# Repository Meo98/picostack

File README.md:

<h1 align="center">PicoStack</h1>

<p align="center">
  <b>Stackable, contract-driven modules for the Raspberry Pi Pico. No module firmware: the Pico drives everything.</b><br>
  Open hardware, generated by code, verified by tests that are proven to fail.
</p>

<p align="center">

</p>

---

**One board plus a Pico is a working device.** Every PicoStack module is a
74 × 58 mm board with two 1×20 stacking sockets in the Pico's own geometry.
The Pico plugs into the top of the stack; all 40 pins run down through it.
Each module carries its own 6–30 V input (reverse-polarity protection,
TVS, a 3 A buck to 5 V, a Schottky into VSYS), so you can also just power
the Pico over USB while you program it and the module's logic is live.

**v3 is deliberately dumb.** v1/v2 gave every module its own microcontroller,
a token chain to address it and a bootloader path to flash it through the
stack. None of that ever ran on a desk, and none of it was needed for the
exhibits this was built for. v3 removes it: the Pico drives each channel
directly through a GPIO *bank*. The 16 PWM-capable pins GP7–GP22 are split
into four banks (A–D) of four; a module picks its bank with a 0603 solder
matrix on the board (factory default: motor = A, dimmer = B, so one motor
and one dimmer stack without touching an iron). GP26–28 serve analog
signals, GP4/GP5 come out as a Qwiic port, GP6 is a wired-AND emergency
stop, GP0–GP3 sit on a user header.

```python
import picostack                      # firmware/pico/picostack.py (MicroPython)
led = picostack.Dimmer(kanaele=4)     # bank B by default
led.set(1, 0.5)                       # channel 1 at 50 %
```

**The unusual part: these boards are not drawn, they are built.**
Schematics, placement, routing, ground stitching and the manufacturing
checks all come from Python that runs headless against KiCad. The stack's
mechanical and electrical rules live in one machine-readable file, the
*contract* ([`tools/stack_spec.py`](tools/stack_spec.py), rendered as
[docs/vertrag.md](docs/vertrag.md)), and every board is measured against it
before it may exist. The full v3 rationale is in the
[design spec](docs/superpowers/specs/2026-11-15-picostack-v3-design.md).

## Boards (v3, contract v4)

| Board | What it does | State |
|---|---|---|
| Dimmer1 / Dimmer3 / Dimmer4 | 1, 3 or 4 low-side PWM channels, 3 A each (4 A per module), screw terminals | routed, DRC 0/0, fab files in `hardware/fertigung/` |
| Motor | DRV8876 H-bridge, 2.5 A, hardware emergency stop, current sense on GP26 | next: rebuilt on the v3 contract |

Placement follows the current, not the autorouter: FETs sit right above
their terminals (tab down, leads up), free-wheel diodes above the FETs,
the buck converter under the Pico at the USB end, the 4 A trunk is
pre-wired by hand (1.4 mm) and the router only fills in the signals.
The Pico W antenna zone between the socket rows is copper-free on both
layers.

## Why you might care

- **You want motorized / sensor / whatever hats for the Pico** that stack
  instead of sprawling across a desk, with industrial-ish screw terminals
  and a 6–30 V input, and you'd rather not maintain firmware for a second
  microcontroller on every board.
- **You want to see a fully generative KiCad workflow**: schematic
  generators, a hand-placed description, headless routing
  ([KiCadRoutingTools](https://github.com/drandyhaas/KiCadRoutingTools)),
  copper-pour healing (`tools/pcb/masseheiler.py`), DRC and a
  current-capacity gate that walks every power net's real copper path
  (`tools/pcb/strombelastung.py`), all from the command line
  (`tools/pcb/verlegen_v3.sh dimmer4`).
- **You like tests that can actually fail.** Every check in this repository
  ships with a proof that it turns red when the thing it guards is broken.
  ERC and DRC caught *none* of the real bugs found during development,
  including a fail-unsafe emergency-stop gate, a reverse-polarity FET wired
  as a crowbar, a 0.25 mm neck in a 4 A trunk, and a board height at which
  a module mounted upside-down would have plugged in. See
  [tests/](tests/) and `tests/run_all.py`.

## Repository layout

```text
tools/stack_spec.py   the contract (v4)
tools/sch/            schematic generators (versorgung.py, dimmermodul.py)
tools/pcb/            placement descriptions, build.py, router driver, probes
tools/fertigung.sh    gerbers + BOM/CPL for JLCPCB
tests/                plain-python suites (no pytest needed), tests/run_all.py
firmware/pico/        MicroPython library for the Pico
hardware/kicad/       generated .kicad_sch + built .kicad_pcb per board
hardware/fertigung/   gerber zip, jlc-bom.csv, jlc-cpl.csv per board
docs/                 project website, vertrag.md, specs
```

## Building the boards yourself

You need KiCad 10, Python 3, and
[KiCadRoutingTools](https://github.com/drandyhaas/KiCadRoutingTools)
(with numpy/scipy/shapely; `verlegen_v3.sh` wraps it in a nix-shell).

```bash
python3 tests/run_all.py                 # every suite, no board tools needed
tools/pcb/verlegen_v3.sh dimmer4         # schematic -> board -> routed -> DRC + probes
tools/fertigung.sh dimmer4               # gerbers, BOM, CPL
```

## Getting boards made

Gerbers, JLC-format BOM/CPL and the list of hand-populated parts for all
three dimmer boards live under `hardware/fertigung/{dimmer1,dimmer3,dimmer4}/`.
[`hardware/fertigung/ORDERING.md`](hardware/fertigung/ORDERING.md) walks
through ordering an assembled board at JLCPCB. The stacking headers
(Pimoroni Pico Stacking Headers, 1×20 and a 1×4 cut from one) and the user
header are soldered by hand, in the plugged-together stack, so the contacts
line up without strain. **No v3 board has been manufactured yet.**

## Contributing a module

A module is a 74 × 58 mm board that keeps the contract: socket rows and
power row on their contract positions, terminals flush with the bottom
edge, nothing taller than 8 mm under the Pico, the antenna zone free, and
a bank matrix for its signals. Start by copying
`tools/pcb/spec_dimmer_basis.py` and `tools/sch/dimmermodul.py`, then read
[CONTRIBUTING.md](CONTRIBUTING.md).

## License

- **Hardware** (everything under `hardware/`): [CERN-OHL-S-2.0](hardware/LICENSE).
- **Code** (tools, generators, firmware): [GPL-3.0-or-later](LICENSE).
- **Documentation**: CC-BY-SA 4.0.

## Project language

The public face of this project is English. Code comments are German,
they carry the engineering rationale of every decision. New contributions
should be in English.

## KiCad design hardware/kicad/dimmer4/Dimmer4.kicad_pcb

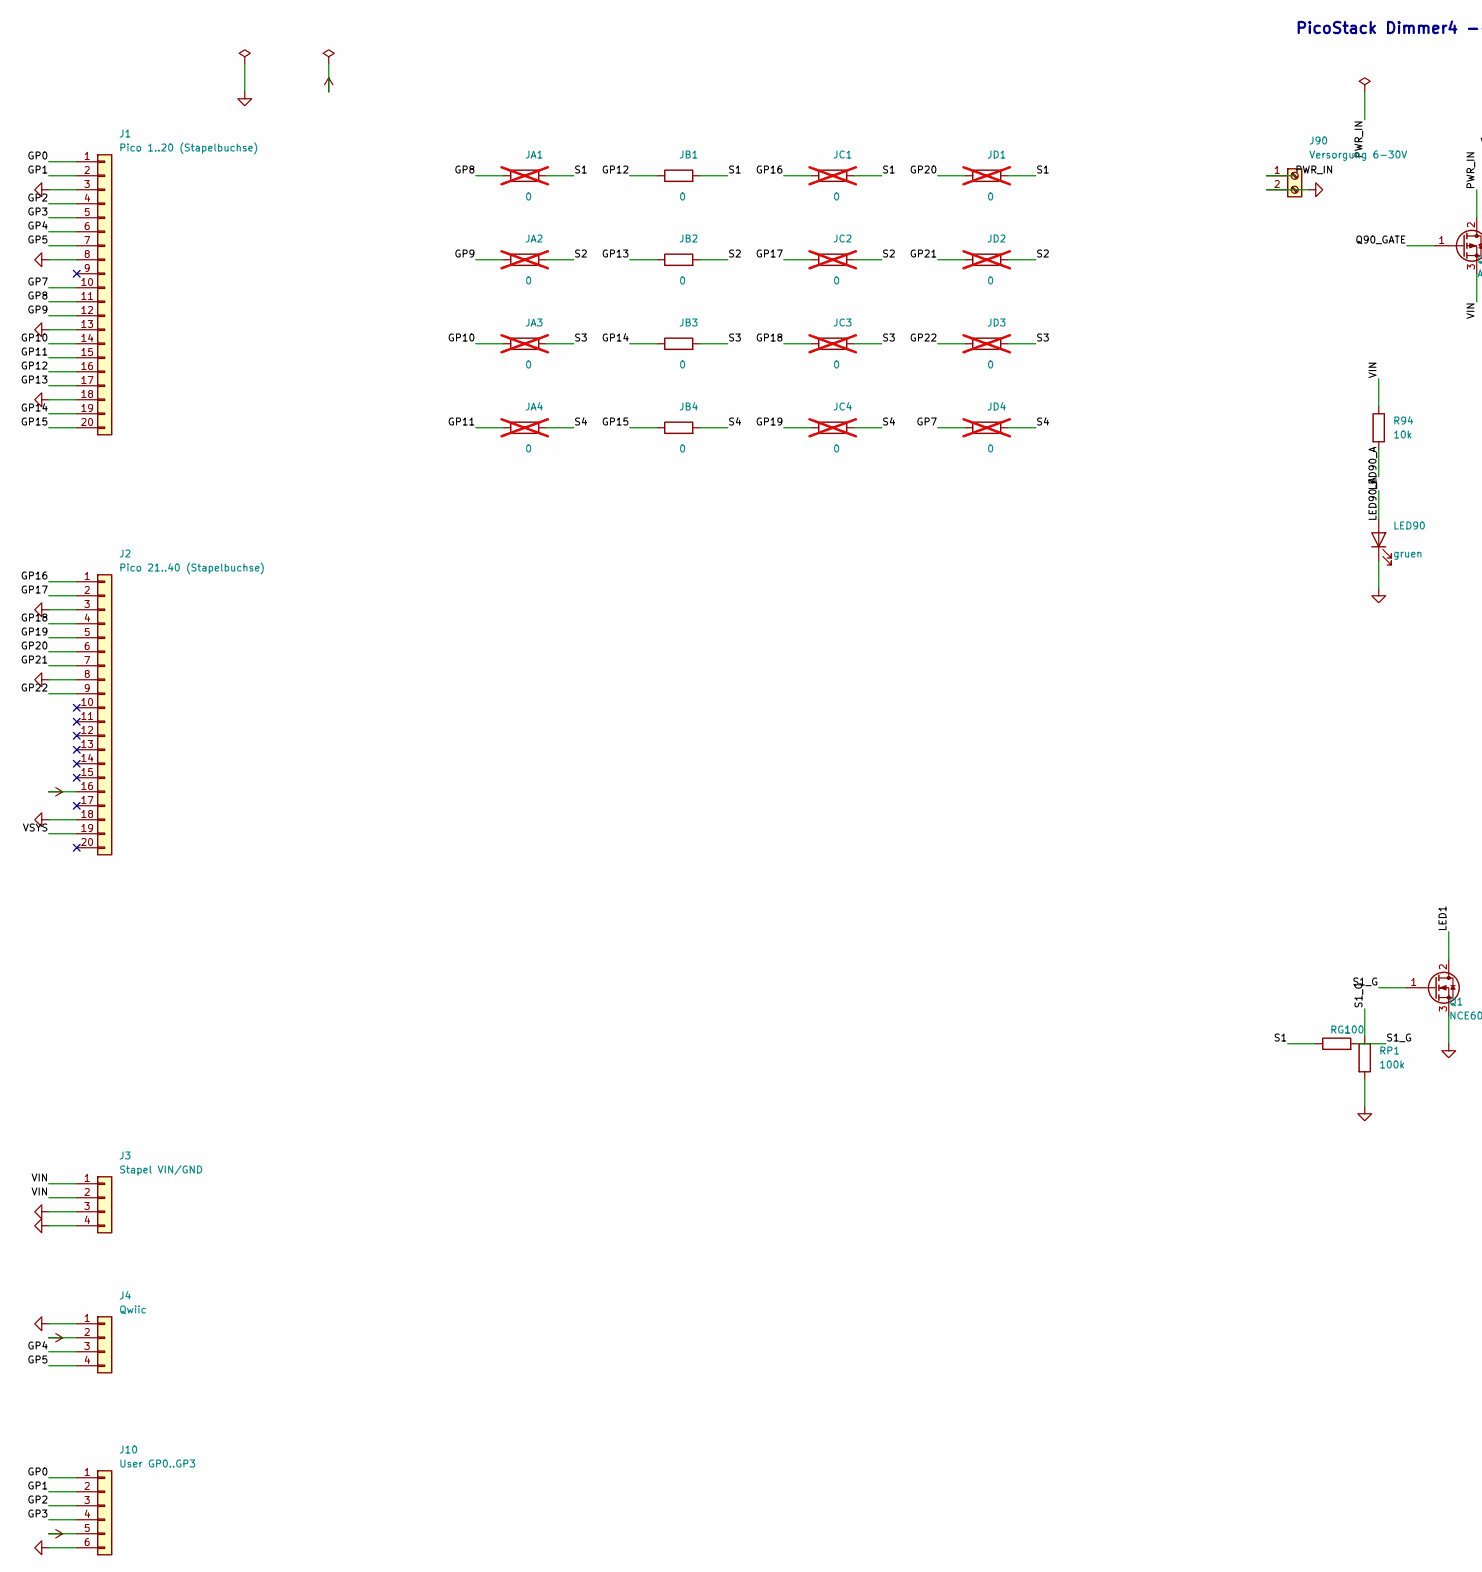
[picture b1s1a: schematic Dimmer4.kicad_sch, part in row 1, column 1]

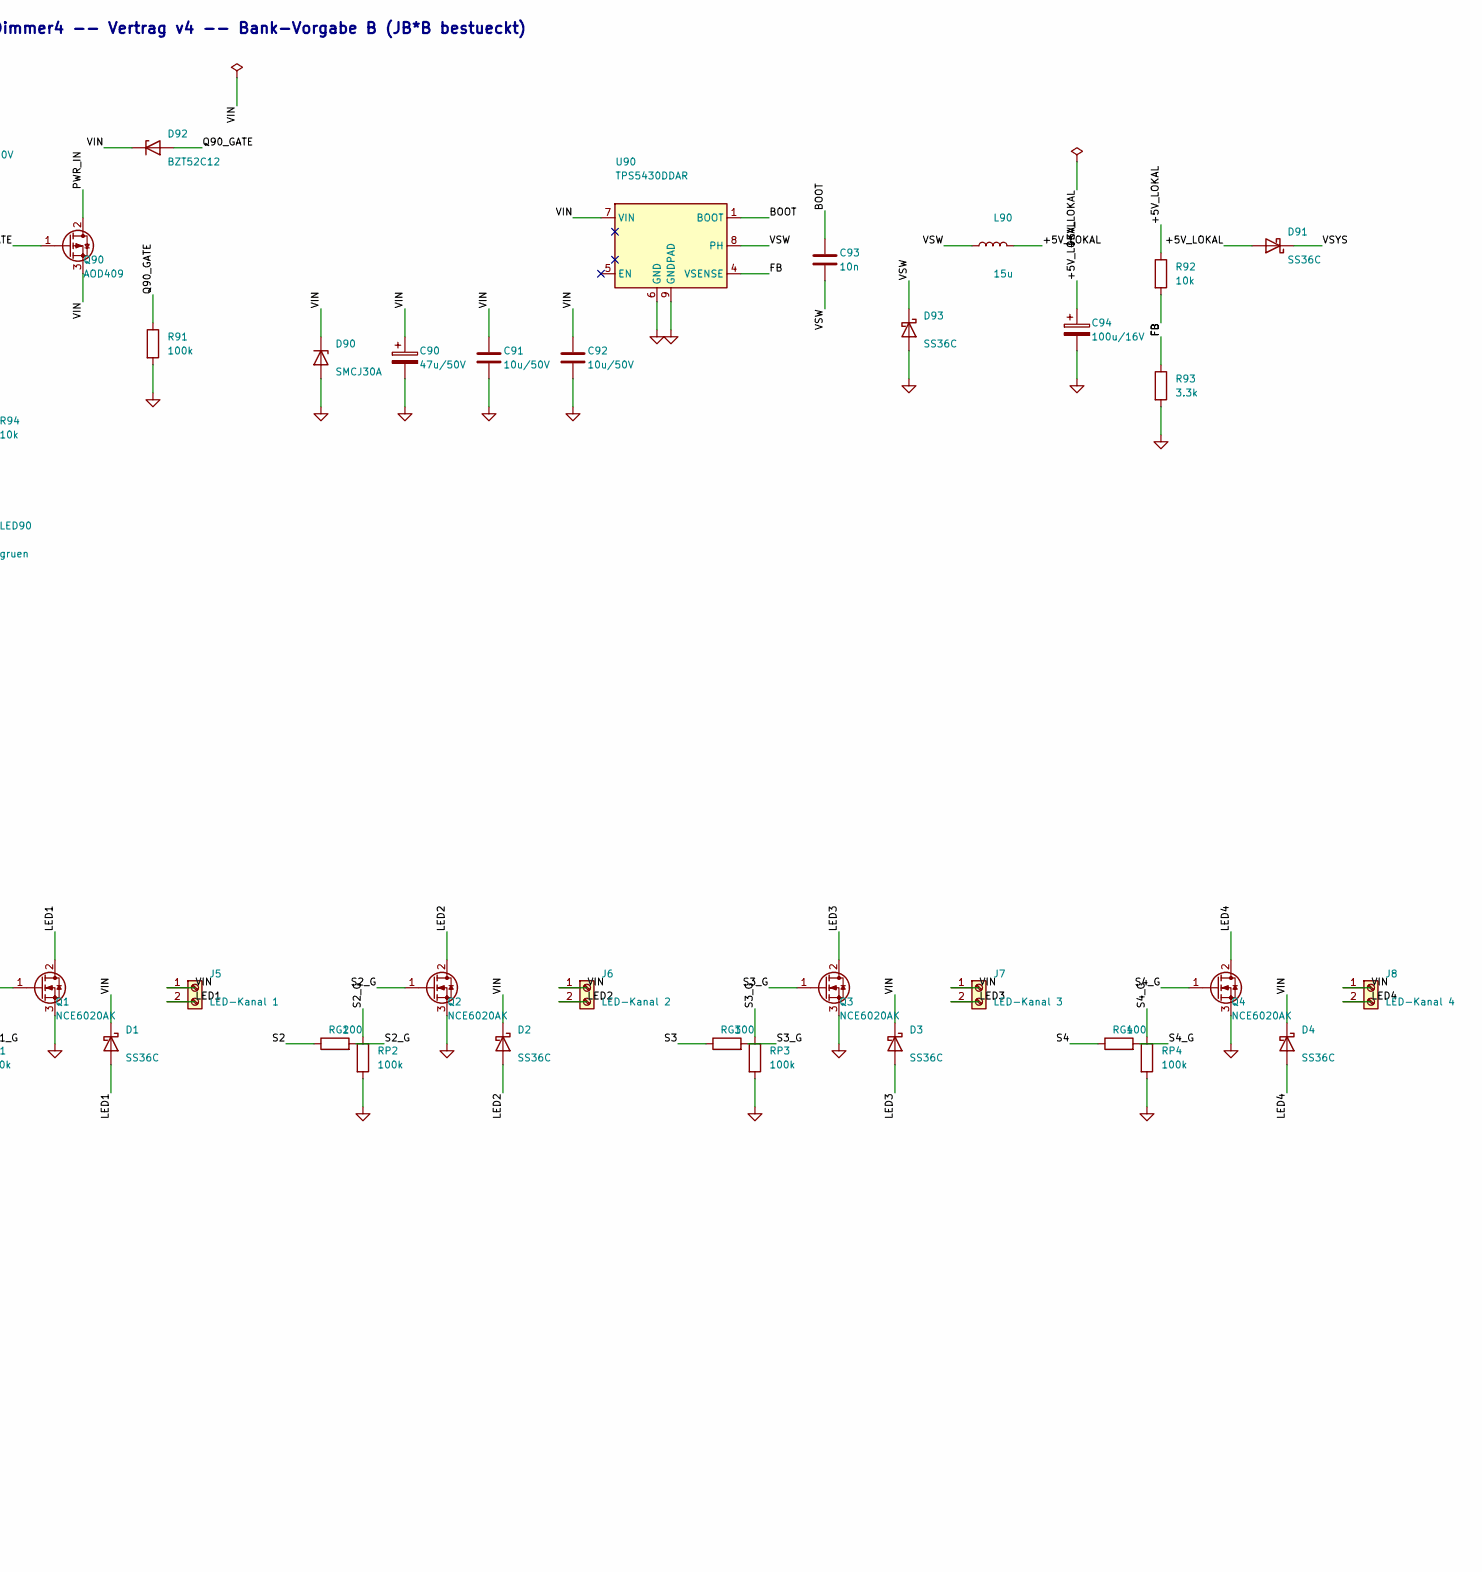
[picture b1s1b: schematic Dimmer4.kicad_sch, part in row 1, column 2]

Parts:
C90: 47u/50V; CP_Elec_6.3x7.7
C91, C92: 10u/50V; C_1210_3225Metric
C93: 10n; C_0805_2012Metric
C94: 100u/16V; CP_Elec_6.3x7.7
D1, D2, D3, D4, D91, D93: SS36C; D_SMC; LCSC C16237
D90: SMCJ30A; D_SMC; LCSC C340696
D92: BZT52C12; D_SOD-123; LCSC C19077410
J1: Pico 1..20 (Stapelbuchse); PinSocket_1x20_P2.54mm_Vertical
J2: Pico 21..40 (Stapelbuchse); PinSocket_1x20_P2.54mm_Vertical
J3: Stapel VIN/GND; PinSocket_1x04_P2.54mm_Vertical
J4: Qwiic; JST_SH_SM04B-SRSS-TB_1x04-1MP_P1.00mm_Horizontal
J5: LED-Kanal 1; TerminalBlock_Phoenix_PT-1,5-2-3.5-H_1x02_P3.50mm_Horizontal; LCSC C474892
J6: LED-Kanal 2; TerminalBlock_Phoenix_PT-1,5-2-3.5-H_1x02_P3.50mm_Horizontal; LCSC C474892
J7: LED-Kanal 3; TerminalBlock_Phoenix_PT-1,5-2-3.5-H_1x02_P3.50mm_Horizontal; LCSC C474892
J8: LED-Kanal 4; TerminalBlock_Phoenix_PT-1,5-2-3.5-H_1x02_P3.50mm_Horizontal; LCSC C474892
J10: User GP0..GP3; PinHeader_1x06_P2.54mm_Vertical
J90: Versorgung 6-30V; TerminalBlock_Phoenix_PT-1,5-2-3.5-H_1x02_P3.50mm_Horizontal; LCSC C474892
JA1, JA2, JA3, JA4: 0; R_0603_1608Metric; LCSC C21189; not fitted
JB1, JB2, JB3, JB4: 0; R_0603_1608Metric; LCSC C21189
JC1, JC2, JC3, JC4: 0; R_0603_1608Metric; LCSC C21189; not fitted
JD1, JD2, JD3, JD4: 0; R_0603_1608Metric; LCSC C21189; not fitted
L90: 15u; L_Sunlord_SWPA6045S; LCSC C83374
LED90: gruen; LED_0805_2012Metric
Q1, Q2, Q3, Q4: NCE6020AK; TO-252-3_TabPin2; LCSC C108639
Q90: AOD409; TO-252-3_TabPin2; LCSC C36220
R91: 100k; R_0805_2012Metric; LCSC C149504
R92: 10k; R_0603_1608Metric; LCSC C25804
R93: 3.3k; R_0603_1608Metric; LCSC C22978
R94: 10k; R_0805_2012Metric; LCSC C17414
RG1, RG2, RG3, RG4: 100; R_0603_1608Metric; LCSC C22775
RP1, RP2, RP3, RP4: 100k; R_0603_1608Metric; LCSC C25803
U90: TPS5430DDAR; SOIC-8-1EP_3.9x4.9mm_P1.27mm_EP2.29x3mm; LCSC C9864

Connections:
3V3: J2.16, J4.2, J10.5
/+5V_LOKAL: C94.1, D91.2 (A), L90.2, R92.1
/BOOT: C93.1, U90.1 (BOOT)
/FB: R92.2, R93.1, U90.4 (VSENSE)
/GP0: J1.1, J10.1
/GP1: J1.2, J10.2
/GP2: J1.4, J10.3
/GP3: J1.5, J10.4
/GP4: J1.6, J4.3
/GP5: J1.7, J4.4
/GP7: J1.10, JD4.1
/GP8: J1.11, JA1.1
/GP9: J1.12, JA2.1
/GP10: J1.14, JA3.1
/GP11: J1.15, JA4.1
/GP12: J1.16, JB1.1
/GP13: J1.17, JB2.1
/GP14: J1.19, JB3.1
/GP15: J1.20, JB4.1
/GP16: J2.1, JC1.1
/GP17: J2.2, JC2.1
/GP18: J2.4, JC3.1
/GP19: J2.5, JC4.1
/GP20: J2.6, JD1.1
/GP21: J2.7, JD2.1
/GP22: J2.9, JD3.1
/LED1: D1.2 (A), J5.2, Q1.2 (D)
/LED2: D2.2 (A), J6.2, Q2.2 (D)
/LED3: D3.2 (A), J7.2, Q3.2 (D)
/LED4: D4.2 (A), J8.2, Q4.2 (D)
/LED90_A: LED90.2 (A), R94.2
/PWR_IN: J90.1, Q90.2 (D)
/Q90_GATE: D92.2 (A), Q90.1 (G), R91.1
/S1: JA1.2, JB1.2, JC1.2, JD1.2, RG1.1
/S1_G: Q1.1 (G), RG1.2, RP1.1
/S2: JA2.2, JB2.2, JC2.2, JD2.2, RG2.1
/S2_G: Q2.1 (G), RG2.2, RP2.1
/S3: JA3.2, JB3.2, JC3.2, JD3.2, RG3.1
/S3_G: Q3.1 (G), RG3.2, RP3.1
/S4: JA4.2, JB4.2, JC4.2, JD4.2, RG4.1
/S4_G: Q4.1 (G), RG4.2, RP4.1
/VIN: C90.1, C91.1, C92.1, D1.1 (K), D2.1 (K), D3.1 (K), D4.1 (K), D90.1 (K), D92.1 (K), J3.1, J3.2, J5.1, J6.1, J7.1, J8.1, Q90.3 (S), R94.1, U90.7 (VIN)
/VSW: C93.2, D93.1 (K), L90.1, U90.8 (PH)
/VSYS: D91.1 (K), J2.19
GND: C90.2, C91.2, C92.2, C94.2, D90.2 (A), D93.2 (A), J1.3, J1.8, J1.13, J1.18, J2.3, J2.8, J2.18, J3.3, J3.4, J4.1, J10.6, J90.2, LED90.1 (K), Q1.3 (S), Q2.3 (S), Q3.3 (S), Q4.3 (S), R91.2, R93.2, RP1.2, RP2.2, RP3.2, RP4.2, U90.6 (GND), U90.9 (GNDPAD)

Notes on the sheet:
PicoStack Dimmer4 -- Vertrag v4 -- Bank-Vorgabe B (JB*B bestueckt)

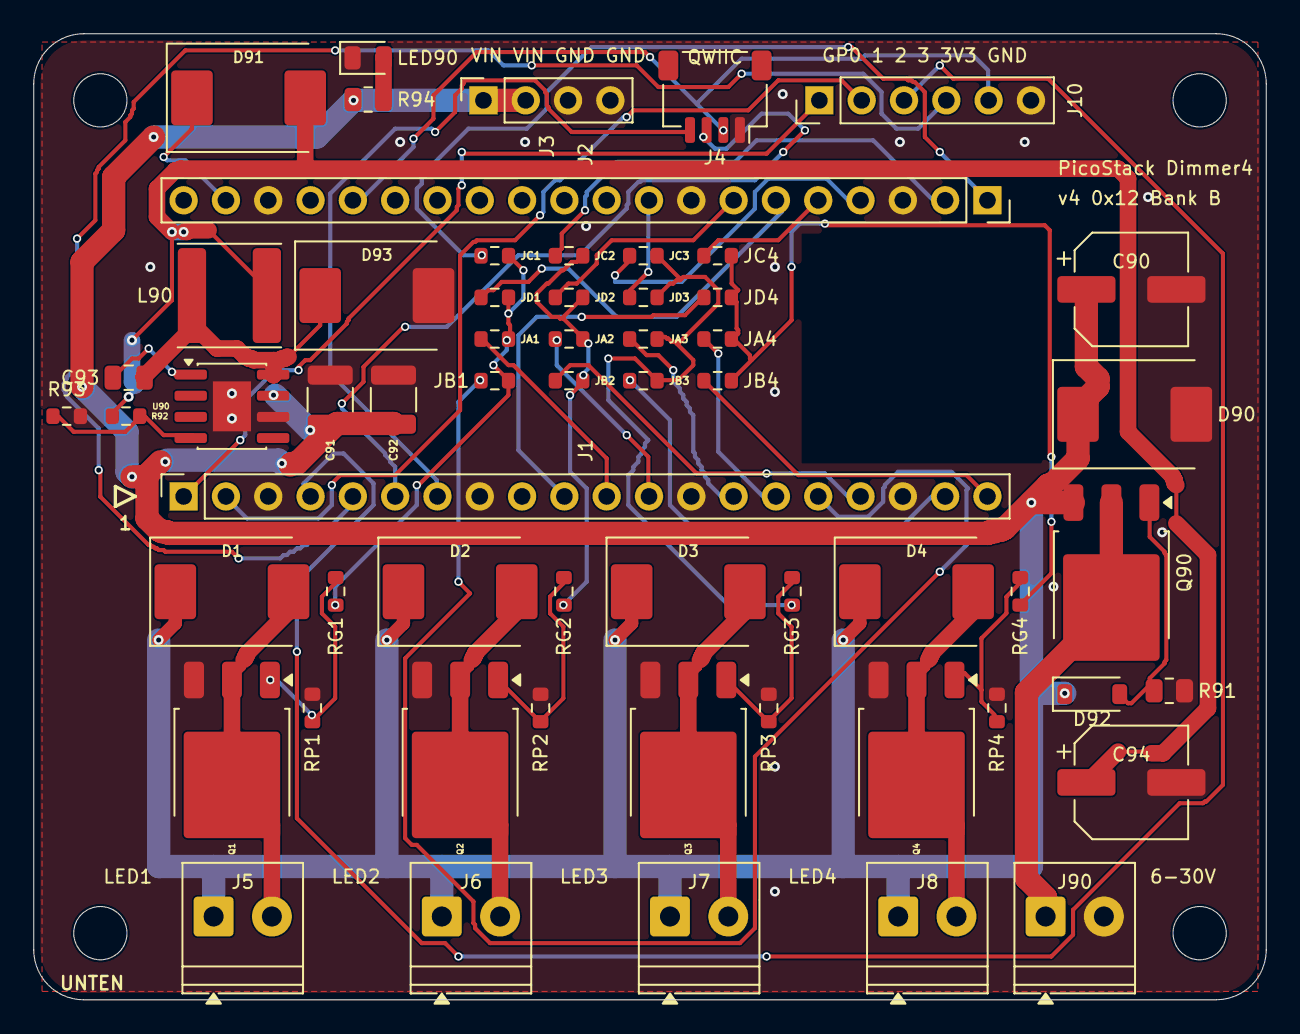
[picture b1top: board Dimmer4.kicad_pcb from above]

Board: 2 copper layers, 74.0 x 58.0 mm, 63 parts (0 on the bottom side), 45 nets.

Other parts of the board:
H1, H2, H3, H4: M3

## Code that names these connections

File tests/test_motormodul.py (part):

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
# ------------------------------- Punkt 4: die PEGEL der Notaus-Verriegelung
# Diese Zusicherungen pruefen nicht, ob ein Bauteil da ist, sondern welche
# SPANNUNG am nSLEEP-Pin des DRV8876 tatsaechlich ansteht. Genau daran
# scheiterte die erste Fassung: sie hatte eine Diode, aber keinen Pegel.
# Alle Groessen kommen aus tools/sch/motormodul.py; dort steht zu jeder die
# Datenblattquelle mit Dokumentnummer und Abschnitt.
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    Ein haengender Modul-MCU treibt ueber `r_vor` aktiv HIGH; die Klemme
    zieht ueber `r_serie` gegen `v_klemme` (= Busspannung + Vorwaerts-
    spannung der Klemmdiode). `rpd` ist der interne Pulldown des
    DRV8876-nSLEEP-Pins. Knotengleichung:

        (v_quelle - U)/r_vor = (U - v_klemme)/r_serie + U/rpd

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# --- Gegenprobe 2: R14 weg, R9 gross -- ZWEI Diodenspannungen in Reihe ---
# Der Bus geht nicht auf 0 V, sondern liegt selbst eine Diodenspannung
# ueber Masse (D3/D4 gegen den Schaltkontakt). Eine zweite Diode zum
# nSLEEP-Pin addiert die naechste.
_u_ohne_r14 = _nsleep_diodenklemme(10e3, 0.0, 2 * M.ALT_VF_1N4148)
check("Gegenprobe: Klemme ohne R14 (R9=10k) bleibt trotzdem ueber VIL",
      _u_ohne_r14 > M.DRV_VIL_MAX, True)
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
    # NFAULT und IPROPI haben laut Aufgabenbrief KEINEN Vorwiderstand --
    # DRV8876, Pullup/Filter und MCU teilen sich direkt ein Netz.
    _an_nfault = set(_netz_pins(_sch, _gen, modulsockel.NETZE_NACH_AUSSEN["NFAULT"]))
    check("NFAULT erreicht U100 (MCU-Eingang)", ("U100", "12") in _an_nfault, True)
    check("NFAULT erreicht U1 Pin 4 (DRV8876 ~NFAULT)", ("U1", "4") in _an_nfault, True)
    check("NFAULT traegt den Pullup R13", ("R13", "2") in _an_nfault, True)

    _an_ipropi = set(_netz_pins(_sch, _gen, modulsockel.NETZE_NACH_AUSSEN["IPROPI"]))
    # PA6 traegt laut STM32C011-Datenblatt (DS13866, Tabelle 12 "Pin
    # assignment and description") die Zusatzfunktion ADC_IN6 -- per
    # WebSearch-Auszug aus der Tabelle bestaetigt (zwei unabhaengige
    # Fundstellen), keine selbst geoeffnete PDF-Seite (st.com blockiert
    # den direkten Download mit HTTP/2 INTERNAL_ERROR, dieselbe
    # Einschraenkung wie hardware/bauteile.md, Beleg 1, dort dokumentiert).
    check("IPROPI erreicht U100 Pin 13 (PA6 -- ADC_IN6, DS13866 Tabelle 12)",
          ("U100", "13") in _an_ipropi, True)
    check("IPROPI erreicht U1 Pin 6 (DRV8876 IPROPI-Ausgang)",
          ("U1", "6") in _an_ipropi, True)
    check("IPROPI traegt R5 (bestueckt, s.o.)", ("R5", "1") in _an_ipropi, True)
    check("IPROPI traegt R10 (DNP)", ("R10", "1") in _an_ipropi, True)
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    # der Beweis, dass motormodul.bauen() versorgung.bauen() nicht nur
    # aufruft, sondern auch richtig verdrahtet einbindet.
    check("Q90-Drain (Schutz) an der Einspeisung PWR_IN",
          ("Q90", "2") in set(_netz_pins(_sch, _gen, "PWR_IN")), True)
    check("Q90-Source (Schutz) an der lokalen Schiene +24V",
          ("Q90", "3") in _an_24v, True)
    check("Gate-Teiler R90 an der lokalen Schiene +24V",
          ("R90", "2") in _an_24v, True)
    _an_vsys = set(_netz_pins(_sch, _gen, "VSYS"))
    check("VSYS nur ueber die Diode D91, nicht direkt vom Regler U90",
          ("D91", "1") in _an_vsys and not any(r == "U90" for r, _ in _an_vsys),
          True)
    # Fix-Runde 1 (Task-5-Review, 2026-09-08): VSYS (Pico-Pin 39, J105
    # Kontakt 19) ist seit stack_spec.IST_BELEGBAR(39) == True kein
    # no_connect mehr, sondern erreicht ueber den Stapelstecker denselben
    # Knoten wie D91 -- genau der Verbraucher, dessen Fehlen vorher die
    # isolated_pin_label-ERC-Warnung ausloeste (s. ERC-Abschnitt unten).
    check("J105 Kontakt 19 (Pico-Pin 39, VSYS) erreicht D91 statt "
          "no_connect zu bleiben", ("J105", "19") in _an_vsys, True)

    # -------------------- Task 5: Stapel-PWR24V speist die lokale Schiene
    # `_stapel_speist_lokal()` bindet "PWR24V" (Leistungsstecker J103/
    # J104) und "+24V" (hinter Q90) elektrisch zu einem Knoten, indem sie
    # EINEN Draht zwischen einem "+24V"- und einem "PWR24V"-Label zieht
    # (s. dortiger Docstring). `_netz_pins()` (woertlich aus
    # tests/test_modulsockel.py uebernommen) folgt dabei bewusst nur EINEM
    # Drahtschritt ab einem Labelpunkt -- es ist kein vollstaendiger
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    # STRUKTUR des Drahts selbst gegen `sch.WIRES`/`sch.LABELS` geprueft --
    # eine Ebene tiefer als `_netz_pins()`, aber unmittelbar am Datenmodell,
    # das auch `kicad-cli` letztlich sieht.
    _an_pwr24v = set(_netz_pins(_sch, _gen, "PWR24V"))
    check("J103 bleibt (nur) ueber das Label PWR24V erreichbar",
          any(r == "J103" for r, _ in _an_pwr24v), True)
    check("Q90 (Source) bleibt (nur) ueber das Label +24V erreichbar",
          ("Q90", "3") in _an_24v, True)
    _labels_24v = {(x, y) for x, y, _r, txt in _sch.LABELS if txt == "+24V"}
    _labels_pwr24v = {(x, y) for x, y, _r, txt in _sch.LABELS if txt == "PWR24V"}
    _direkt_verbunden = any(
        (a in _labels_24v and b in _labels_pwr24v)
        or (b in _labels_24v and a in _labels_pwr24v)
        for a, b in _sch.WIRES)
    check("ein Draht verbindet ein +24V-Label direkt mit einem PWR24V-"
          "Label (_stapel_speist_lokal) -- ERC bestaetigt zusaetzlich die "
          "daraus folgende elektrische Gleichsetzung (s. "
          "ERWARTETE_ERC_WARNUNGEN unten)", _direkt_verbunden, True)
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    # Die Sammelleitung erreicht den Stapelstecker (global) UND die
    # Hardware-Verriegelung (U3, wirkt auf U1_NSLEEP unabhaengig vom MCU)
    # UND die zwei Open-Drain-Treiber der Ruhestrom-Kanaele (U6/U7).
    _an_notaus = set(_netz_pins(_sch, _gen, modulsockel.NETZE_NACH_AUSSEN["NOTAUS"]))
    check("NOTAUS erreicht den Stapelstecker (J100 Pin 9)",
          ("J100", "9") in _an_notaus, True)
    check("NOTAUS erreicht U3 Pin 2 (Eingang B des Verriegelungsgatters)",
          ("U3", "2") in _an_notaus, True)
    check("NOTAUS traegt den Pullup R15", ("R15", "2") in _an_notaus, True)
    check("NOTAUS erreicht NICHT direkt U1 (der Weg fuehrt ueber das "
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          any(ref == "U1" for ref, _ in _an_notaus), False)
    # Aufgabe 5d: der Bus wird von den zwei Open-Drain-Ausgaengen gezogen,
    # nicht mehr von Koppeldioden an einem Schaltkontakt.
    check("NOTAUS wird von U6 Pin 4 gezogen (Open-Drain, Kanal 1)",
          ("U6", "4") in _an_notaus, True)
    check("NOTAUS wird von U7 Pin 4 gezogen (Open-Drain, Kanal 2)",
          ("U7", "4") in _an_notaus, True)
    check("auf NOTAUS haengt nichts ausser Stecker, Pullup, "
          "Verriegelungsgatter und den zwei Kanaltreibern",
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    check("J3 hat vier Pole -- zwei Adern je Kanal", len(_j3_pins), 4)

    # Die zwei Kanaele bleiben elektrisch GETRENNT bis auf den Bus.
    _an_schleife1 = set(_netz_pins(_sch, _gen, "SCHLEIFE_1"))
    _an_schleife2 = set(_netz_pins(_sch, _gen, "SCHLEIFE_2"))
    check("SCHLEIFE_1 und SCHLEIFE_2 sind verschiedene Netze",
          _an_schleife1.isdisjoint(_an_schleife2), True)
    check("U100 Pin 3 (PC15) liest Kanal 1", ("U100", "3") in _an_schleife1, True)
    check("U100 Pin 14 (PA7) liest Kanal 2", ("U100", "14") in _an_schleife2, True)
    for _kanal, (_pins, _opto, _rpd, _inv) in enumerate((
            (_an_schleife1, "U4", "R20", "U6"),
            (_an_schleife2, "U5", "R21", "U7")), start=1):
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          M.GATTER_VOH_MIN > M.DRV_VIH_MIN, True)

    # Die Verriegelung sitzt IM Signalweg zwischen MCU und DRV8876: der
    # MCU erreicht den Treiber-nSLEEP-Pin nur noch ueber das Gatter.
    # Das Netz U1_NSLEEP darf deshalb GENAU zwei Pins tragen -- den
    # Gatterausgang und den Treibereingang. Haengt dort noch etwas
    # anderes (etwa eine wieder eingebaute Diodenklemme R14/D2), ist die
    # Gegentaktstufe des Gatters nicht mehr allein bestimmend und diese
    # Zusicherung wird rot.
    _an_u1_nsleep = set(_netz_pins(_sch, _gen, "U1_NSLEEP"))
    check("U3 Pin 4 (Gatterausgang Y) treibt U1_NSLEEP",
          ("U3", "4") in _an_u1_nsleep, True)
    check("U1 Pin 3 (DRV8876 nSLEEP) haengt auf demselben Netz",
          ("U1", "3") in _an_u1_nsleep, True)
    check("auf U1_NSLEEP haengt NICHTS ausser Gatterausgang und "
          "Treibereingang (kein zweiter Treiber, keine Diodenklemme)",
          _an_u1_nsleep, {("U3", "4"), ("U1", "3")})

    def _u_nsleep_aus_schaltplan(pins_am_netz):
        """Pegel am DRV8876-nSLEEP-Pin im Notaus-Fall, hergeleitet aus
        dem, was laut Schaltplan tatsaechlich auf U1_NSLEEP haengt.

        Treibt dort allein der Gatterausgang, gilt VOL (SCES217AA 5.5).
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          "unter VIL des DRV8876", _u_ist < M.DRV_VIL_MAX, True)

    # Der MCU erreicht das Gatter ueber R9 und sonst nichts.
    _an_gatter_a = set(_netz_pins(_sch, _gen, "NSLEEP_GATTER"))
    check("R9 speist den Gattereingang A", ("R9", "2") in _an_gatter_a, True)
    check("U3 Pin 1 (Eingang A) haengt am selben Netz",
          ("U3", "1") in _an_gatter_a, True)
    check("zwischen R9 und Gattereingang A haengt sonst nichts",
          _an_gatter_a, {("R9", "2"), ("U3", "1")})
    _an_mcu_nsleep = set(_netz_pins(_sch, _gen, modulsockel.NETZE_NACH_AUSSEN["NSLEEP"]))
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
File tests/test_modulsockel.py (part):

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    # 4 und die freien Pins <= 20 sitzen auf J100 (Kontakt == Pico-Pin,
    # s. _stapelstecker()-Docstring), die freien Pins > 20 auf J105
    # (Kontakt == Pico-Pin - 20).
    check("J100 Kontakt 4 (Pico-Pin 4, SEL_OUT) bleibt no_connect",
          _sch.pinpos("J100", "4") in _sch.NOCONN, True)
    for _ref, _p in (("J100", "11"), ("J100", "12"), ("J100", "20"),
                      ("J105", "9"), ("J105", "11"), ("J105", "14")):
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              _sch.pinpos(_ref, _p) in _sch.NOCONN, True)

    # ------------------------------------ Fix-Runde 1 (Task 6, 2026-09-08)
    # PA2..PA6 (U100-Pin "9".."13") sind seit dieser Fix-Runde KEINE
    # unbedingt verdrahteten Motorsignale mehr, sondern -- wie PC14/PC15/
    # PA7/PA8 -- gewoehnliche freie GPIO: `motorsignale=False` (die
    # Vorgabe, hier ueber den unveraenderten Aufruf oben getestet) laesst
    # sie ohne `zusatz_pins`-Eintrag auf no_connect. Vorher (vor der
    # Fix-Runde) waren dieselben fuenf Pins IMMER auf IN1/IN2/NSLEEP/
    # NFAULT/IPROPI verdrahtet -- diese Pruefung waere mit dem alten
    # Verhalten durchgefallen und deckt die Regression damit direkt ab.
    for _p in ("9", "10", "11", "12", "13"):
        check("U100 Pin %s (PA2..PA6, ohne motorsignale/zusatz_pins) "
              "bleibt no_connect" % _p,
              _sch.pinpos("U100", _p) in _sch.NOCONN, True)

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    # weitere Schaltplaene; bricht dort einer der drei Fehler wieder auf,
    # faellt es sonst niemandem auf. Deshalb hier der ERC-Lauf als
    # Testschritt: bauen, exportieren, pruefen, aufraeumen.
    ERWARTETE_ERC_WARNUNGEN = 2  # isolated_pin_label fuer NOTAUS/VSYS --
    # absichtlich einseitige Uebergabenetze, die erst ein echtes Modul
    # (Motormodul: NOTAUS: _notaus_schleifen()/_notaus_verriegelung();
    # VSYS: versorgung.bauen()) auf der Gegenseite schliesst. Steigt
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    # der Test es melden, nicht stillschweigend durchwinken.
    #
    # BIS Fix-Runde 1 (Task 6, 2026-09-08) standen hier 7: IN1/IN2/
    # NSLEEP/NFAULT/IPROPI (Pin 9-13, PA2..PA6) kamen dazu, weil
    # `einbauen(..., mit_flipflop=True)` sie damals UNBEDINGT auf die
    # DRV8876-Motorsignale verdrahtete, unabhaengig vom aufrufenden
    # Modul (auch auf diesem nackten Blatt ohne jeden Motortreiber). Seit
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    # `motorsignale=True`-Gegentest direkt darunter, der die alten 5
    # Warnungen gezielt wieder herstellt (s. dort).
    #
    # VSYS (Pin 39, seit Fix-Runde 1/Task-5-Review, 2026-09-08):
    # stack_spec.IST_BELEGBAR(39) ist jetzt True (VERSORGUNG["vsys_diode"]
    # verlangt genau diese Einspeisung durch jede Versorgungszelle, s.
    # stack_spec.py-Kommentar), also verdrahtet _stapelstecker() den Pin
    # jetzt statt no_connect auf das Label "VSYS" -- auf diesem nackten
    # Modulsockel-Blatt (kein versorgung.py, kein Pico) bleibt das
    # dieselbe Art einseitiges Uebergabenetz wie NOTAUS oben, nicht
    # ein neuer Fehler.
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# entscheidet, muss zum Vertrag passen -- fuer BEIDE Aufrufarten.
#
# Gefragt wird der Generator, nicht die erzeugte Datei. Ein Textvergleich
# im .kicad_sch trifft die PINNAMEN des Pico-Symbols ("VSYS", "RUN", ...)
# und meldet jeden dieser Pins als verdrahtet, obwohl nur das Symbol sie
# beschriftet -- ein erster Versuch dieser Pruefung lief genau darauf
# hinein und stand fuenfmal falsch rot.
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    check("%s: kein offener Pin ohne Grund im Vertrag" % _name,
          sorted(p for p in _offen
                 if p not in S.NICHT_BELEGBAR
                 and S.PIN_ROLLE[p] not in ("frei", "SEL_OUT")), [])

# Und die Geometrie selbst: Pico-Pin 1..20 sitzt auf der LINKEN Reihe
# (Kontakt == Pico-Pin), 21..40 auf der RECHTEN (Kontakt == Pico-Pin-20)
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
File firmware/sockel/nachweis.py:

"""Beschreibt einen Modul-MCU vom Pico aus. Nachweis, kein Produkt.

Reihenfolge: ueber die Kettenlogik in den Bootlader bringen,
synchronisieren, loeschen, blockweise schreiben, ueber dieselbe
Kettenlogik zurueck in die Anwendung.

Auf dem Tischaufbau gibt es weder Flipflop noch Gatter: Pico und MCU
sind ueber vier blanke Draehte verbunden (siehe
docs/nachweis-2026-08.md). Die Pico-UART-Pins entsprechen
FLASH_TX/FLASH_RX aus stack_spec.PIN_ROLLE (Steckerpins 1/2) und
fuehren direkt zum Bootlader-USART der MCU (physisch PA11/PA12, siehe
hardware/bauteile.md). BOOT0 und NRST dagegen liegen hier direkt an
den rohen MCU-Pins (PA14/NRST) an, nicht an SEL/SEL_CLK/FLASH_MODE --
auf der fertigen Platine haelt erst ein D-Flipflop die Auswahl (Q) und
ein Gatter leitet daraus mit FLASH_MODE Reset und Bootlader-Auswahl
ab. Beides existiert auf dem Tisch nicht; das eine Modul am Tisch ist
hier von Hand als "ausgewaehlt" gesetzt (q=1).

EHRLICHKEIT: Dieses Programm ist noch nie auf Hardware gelaufen. Es
ist nicht einmal syntaktisch auf einem Pico geprueft -- MicroPython
mit machine.UART gibt es auf dem Entwicklungsrechner nicht.
"""
from machine import Pin, UART
import time
from an3155 import Bootlader
from kette import modul_zustand

BLOCK = 256
START = 0x08000000

# timeout: MicroPython liefert bei Zeitueberschreitung None zurueck,
# was an3155._quittung() als "keine Antwort" meldet. Ohne timeout=
# blockiert read() je nach Port unbestimmt lange -- ein Modul ohne
# bestueckten MCU laesst den Nachweis dann einfach haengen, statt einen
# Fehler zu melden.
# 2000 ms: Die Quittungen auf SYNC und die Schreibbloecke kommen in
# wenigen Millisekunden; der lange Fall ist die Massenloeschung, deren
# Dauer wir nicht nachgeschlagen haben. Der Wert ist deshalb bewusst
# grosszuegig geschaetzt und nicht aus einem Datenblatt hergeleitet --
# er soll nur verhindern, dass ein toter Chip den Aufbau blockiert.
uart = UART(0, baudrate=115200, bits=8, parity=0, stop=1, tx=0, rx=1,
            timeout=2000)
boot0 = Pin(2, Pin.OUT)
nrst = Pin(3, Pin.OUT)


def reset(flash_mode, q):
    """Reset- und BOOT0-Pegel nicht direkt setzen, sondern ueber
    kette.modul_zustand(flash_mode, q) ableiten -- derselben
    Gatterlogik, die auf der fertigen Platine aus FLASH_MODE und dem
    Flipflop-Ausgang Q gebildet wird. Ein direktes Setzen von
    BOOT0/NRST wuerde eine zweite, womoeglich abweichende Logik neben
    die Kettenlogik stellen, die schon gegen die Wahrheitstabelle
    geprueft ist (tests/test_kette.py). So prueft dieser Nachweis am
    Tisch denselben Weg, den spaeter die Gatter in Kupfer ausfuehren --
    nur eben in Software nachgerechnet, weil sie auf dem Tischaufbau
    (noch) fehlen.

    q ist am Tisch von Hand gesetzt: es gibt nur ein Modul und kein
    Schieberegister, das die Auswahl weiterschieben koennte.

    flash_mode=1, q=1 waehlt dieses (einzige) Modul im Flash-Modus:
    reset=0, boot0=1 -- der Bootlader startet.
    flash_mode=0 ist der Normalbetrieb: reset=0, boot0=0 -- die
    Anwendung startet.
    """
    reset_haltung, boot0_ziel, _sel_out = modul_zustand(flash_mode, q)
    boot0.value(boot0_ziel)
    nrst.value(0)
    time.sleep_ms(10)
    nrst.value(0 if reset_haltung else 1)
    time.sleep_ms(50)


def aufspielen(pfad):
    reset(flash_mode=1, q=1)
    bl = Bootlader(uart)
    if not bl.sync():
        raise RuntimeError("keine Antwort vom Bootlader")
    if not bl.erase_all():
        raise RuntimeError("Loeschen abgelehnt")
    with open(pfad, "rb") as f:
        adresse = START
        while True:
            block = f.read(BLOCK)
            if not block:
                break
            if len(block) % 4:
                block += b"\xff" * (4 - len(block) % 4)
            if not bl.write(adresse, block):
                raise RuntimeError("Schreiben abgelehnt bei 0x%08X" % adresse)
            adresse += len(block)
    reset(flash_mode=0, q=0)
    print("aufgespielt:", pfad)

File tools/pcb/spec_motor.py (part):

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    # 60,80 an die KLEMMENZONE -- 25,4 x 11,0 mm, auf keiner anderen
    # Platine dieser Familie belegt). Sie passt zur Pinlage des
    # HTSSOP-16 (nachgemessen am gebauten Brett, Drehung 0):
    #   links  (rel x -2,90): Pins 1..8, die Steuersignale UND /Out1
    #   rechts (rel x +2,90): /Out2, /+24V, /VCP, /CPH, /CPL
    # Die Steuersignale schauen damit auf J105, ueber den sie vom Pico
    # kommen; /+24V schaut nach oben zur Versorgungszelle; /Out1 und
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}

# --- Pflicht-Kennzeichnung (stack_spec.LAYOUT_AUFLAGEN) --------------
# Pin-1-Marke neben Kontakt 1 von stapel_links (Pico-Pin 1, FLASH_TX) --
# der primaere Bezug, weil dort das Pico-Datenblatt selbst Pin 1 zaehlt.
# UNVERAENDERT: stapel_links' pin1 ist Vertrag (frozen), diese Marke
# haengt nicht an BOARD_W/H.
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# "obere Gruppe") -- eine reine Parallelverschiebung aendert an keinem
# Winkel oder Abstand innerhalb der Gruppe etwas.
PRE_TRACKS = (
    # -- /VCP: U1 Pin 12 -> C9 Pad 2, von Hand (Aufgabe D5) ------------
    #
    # WARUM DER ROUTER DAS NICHT KANN. Der /+24V-Stamm kommt von Norden
    # bei x=64,20 herunter und schneidet dann DIAGONAL durch das
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#
# 6-30V (J90, Einspeiseklemme, R7 "Polaritaet wo es zaehlt"): Pin 1
# (x=55,89) fuehrt PWR_IN (+, s. tools/sch/versorgung.py: Q90-Drain an
# PWR_IN), Pin 2 (x=59,39) fuehrt GND (-) -- der KF350/PT-1,5-Footprint
# traegt bereits ein Pfeil-Silkscreen-Dreieck an Pin 1 (Spitze exakt bei
# x=55,89, pcbnew nachgemessen), DIESELBE Konvention wie der eingebaute
# "+" auf C90s CP_Radial-Footprint (Auftrag: "Polaritaet ... wie beim
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
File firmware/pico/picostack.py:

"""PicoStack v3 -- MicroPython-Bibliothek fuer den Raspberry Pi Pico.

Der Pico steckt oben auf dem Stapel; jedes Modul belegt eine GPIO-Bank
(A-D) ueber seine Slot-Matrix. Diese Bibliothek kennt nur den Vertrag
(tools/stack_spec.py): Baenke, ADC-Pins, NOTAUS, I2C.

    import picostack
    led = picostack.Dimmer(bank="B", kanaele=4)
    led.set(1, 0.5)          # Kanal 1 auf 50 %
    led.set(3, 1.0)
    led.aus()

    m = picostack.Motor(bank="A")      # kommt mit dem Motormodul v3
    m.fahren(0.8)                      # vorwaerts 80 %
    m.fahren(-0.3)                     # rueckwaerts 30 %
    print(m.strom_a())                 # aus IPROPI (GP26)

    picostack.notaus_aktiv()           # True = Schleife unterbrochen

Zahlen hier MUESSEN mit tools/stack_spec.py uebereinstimmen; tests/
test_firmware.py prueft das (KiCad-frei, ohne Pico).
"""
try:
    from machine import Pin, PWM, ADC, I2C
except ImportError:          # Host-Tests ohne MicroPython
    Pin = PWM = ADC = I2C = None

VERTRAG_VERSION = 4

BAENKE = {
    "A": (8, 9, 10, 11),
    "B": (12, 13, 14, 15),
    "C": (16, 17, 18, 19),
    "D": (20, 21, 22, 7),
}
ADC_BANK = (26, 27, 28)
BANK_VORGABE = {"Motor": "A", "Dimmer": "B"}
ADC_VORGABE = {"Motor": 26}
NOTAUS_GP = 6
I2C_SDA, I2C_SCL = 4, 5
PWM_HZ = 20000               # ueber dem Hoerbereich; 16 getrennte Kanaele


def bank_pins(bank):
    try:
        return BAENKE[bank]
    except KeyError:
        raise ValueError("Bank %r gibt es nicht (A-D)" % (bank,))


class Dimmer:
    """LED-Dimmer-Modul (1, 3 oder 4 Kanaele), Low-Side-PWM."""

    def __init__(self, bank=None, kanaele=4, hz=PWM_HZ):
        bank = BANK_VORGABE["Dimmer"] if bank is None else bank
        if not 1 <= kanaele <= 4:
            raise ValueError("1..4 Kanaele")
        self.bank = bank
        self.gp = bank_pins(bank)[:kanaele]
        self._pwm = []
        if PWM is not None:
            for gp in self.gp:
                p = PWM(Pin(gp))
                p.freq(hz)
                p.duty_u16(0)
                self._pwm.append(p)

    def set(self, kanal, wert):
        """Kanal 1..n auf 0.0..1.0."""
        if not 1 <= kanal <= len(self.gp):
            raise ValueError("Kanal %d gibt es nicht" % kanal)
        wert = min(1.0, max(0.0, float(wert)))
        if self._pwm:
            self._pwm[kanal - 1].duty_u16(int(wert * 65535))
        return wert

    def aus(self):
        for k in range(1, len(self.gp) + 1):
            self.set(k, 0.0)


class Motor:
    """Motormodul (DRV8876, PH/EN): S1 = EN (PWM), S2 = PH (Richtung),
    S3 = nFAULT (Eingang), S4 = nSLEEP (Freigabe), IPROPI an der ADC-Bank.
    Ohne NOTAUS-Freigabe (Hardware-UND auf dem Modul) laeuft nichts."""

    def __init__(self, bank=None, adc=None, hz=PWM_HZ, ipropi_r_ohm=1300.0):
        bank = BANK_VORGABE["Motor"] if bank is None else bank
        adc = ADC_VORGABE["Motor"] if adc is None else adc
        if adc not in ADC_BANK:
            raise ValueError("ADC-Pin %r nicht in %r" % (adc, ADC_BANK))
        self.bank = bank
        self.gp_en, self.gp_ph, self.gp_fault, self.gp_sleep = bank_pins(bank)
        self.gp_adc = adc
        self._r = ipropi_r_ohm          # 1 mA/A x R -> V
        if PWM is not None:
            self._en = PWM(Pin(self.gp_en))
            self._en.freq(hz)
            self._en.duty_u16(0)
            self._ph = Pin(self.gp_ph, Pin.OUT, value=0)
            self._fault = Pin(self.gp_fault, Pin.IN, Pin.PULL_UP)
            self._sleep = Pin(self.gp_sleep, Pin.OUT, value=1)
            self._adc = ADC(Pin(self.gp_adc))

    def fahren(self, wert):
        """-1.0..1.0; Vorzeichen = Richtung."""
        wert = min(1.0, max(-1.0, float(wert)))
        if PWM is not None:
            self._ph.value(1 if wert >= 0 else 0)
            self._en.duty_u16(int(abs(wert) * 65535))
        return wert

    def stopp(self):
        return self.fahren(0.0)

    def fehler(self):
        return (self._fault.value() == 0) if PWM is not None else False

    def strom_a(self):
        """Motorstrom aus IPROPI: V = I x 1 mA/A x R."""
        if PWM is None:
            return 0.0
        v = self._adc.read_u16() * 3.3 / 65535.0
        return v / (self._r * 1e-3)


def notaus_aktiv():
    """True, wenn NOTAUS (GP6, LOW = gesperrt) ausgeloest ist."""
    if Pin is None:
        return False
    return Pin(NOTAUS_GP, Pin.IN, Pin.PULL_UP).value() == 0


def i2c(freq=400000):
    """Der Qwiic-Bus (GP4/GP5, I2C0)."""
    return I2C(0, sda=Pin(I2C_SDA), scl=Pin(I2C_SCL), freq=freq)

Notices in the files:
README.md:
Code: GPLv3
